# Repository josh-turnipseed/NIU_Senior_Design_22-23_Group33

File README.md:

# NIU Senior Design 2022-2023 Group 33
Analog and Digital Controlled Modular Synthesizer for Audio Synthesis and Signal Processing

The goal of this project was to design and construct a modular Eurorack synthesizer.
The team has designed ten modules that perform the functions of a synthesizer. Those modules are:
- Musical Instrument Digital Interface (MIDI) to Control Voltage (CV)
- Voltage Controlled Oscillator (VCO)
- Voltage Controlled Amplifier (VCA)
- Voltage Controlled Filter (VCF)
- Envelope Generator (EG) ADSR Type
- Low Frequency Oscillator (LFO)
- Mixer
- Multiple
- Attenuverter
- Delay

# Schematics and PCBs
The schematic and board files for all ten modules can be found in the KiCad Schematics folder. In which, are folders for each of the modules. In addition to the KiCad project, schematic, and board files, there is a zip in each module folder which contains all the gerber files required to manufacture the PCBs. This group used JLCPCB, but any manufacture will do.

These files were made using KiCad version 7.0.1, release build

# Front Panels
This group chose to manufacture front panels using FDM 3D printing technologies. Step files can be found in the Steps folder for each of the modules. These files can be loaded into the slicer of your choice. Specifically, this group used Prusaslicer 2.6.0-alpha6 for the embossed text feature. Gcode can be found in the Gcode folder for each of the module front panels with text. The Gcode is for a Prusa i3 MK3S.

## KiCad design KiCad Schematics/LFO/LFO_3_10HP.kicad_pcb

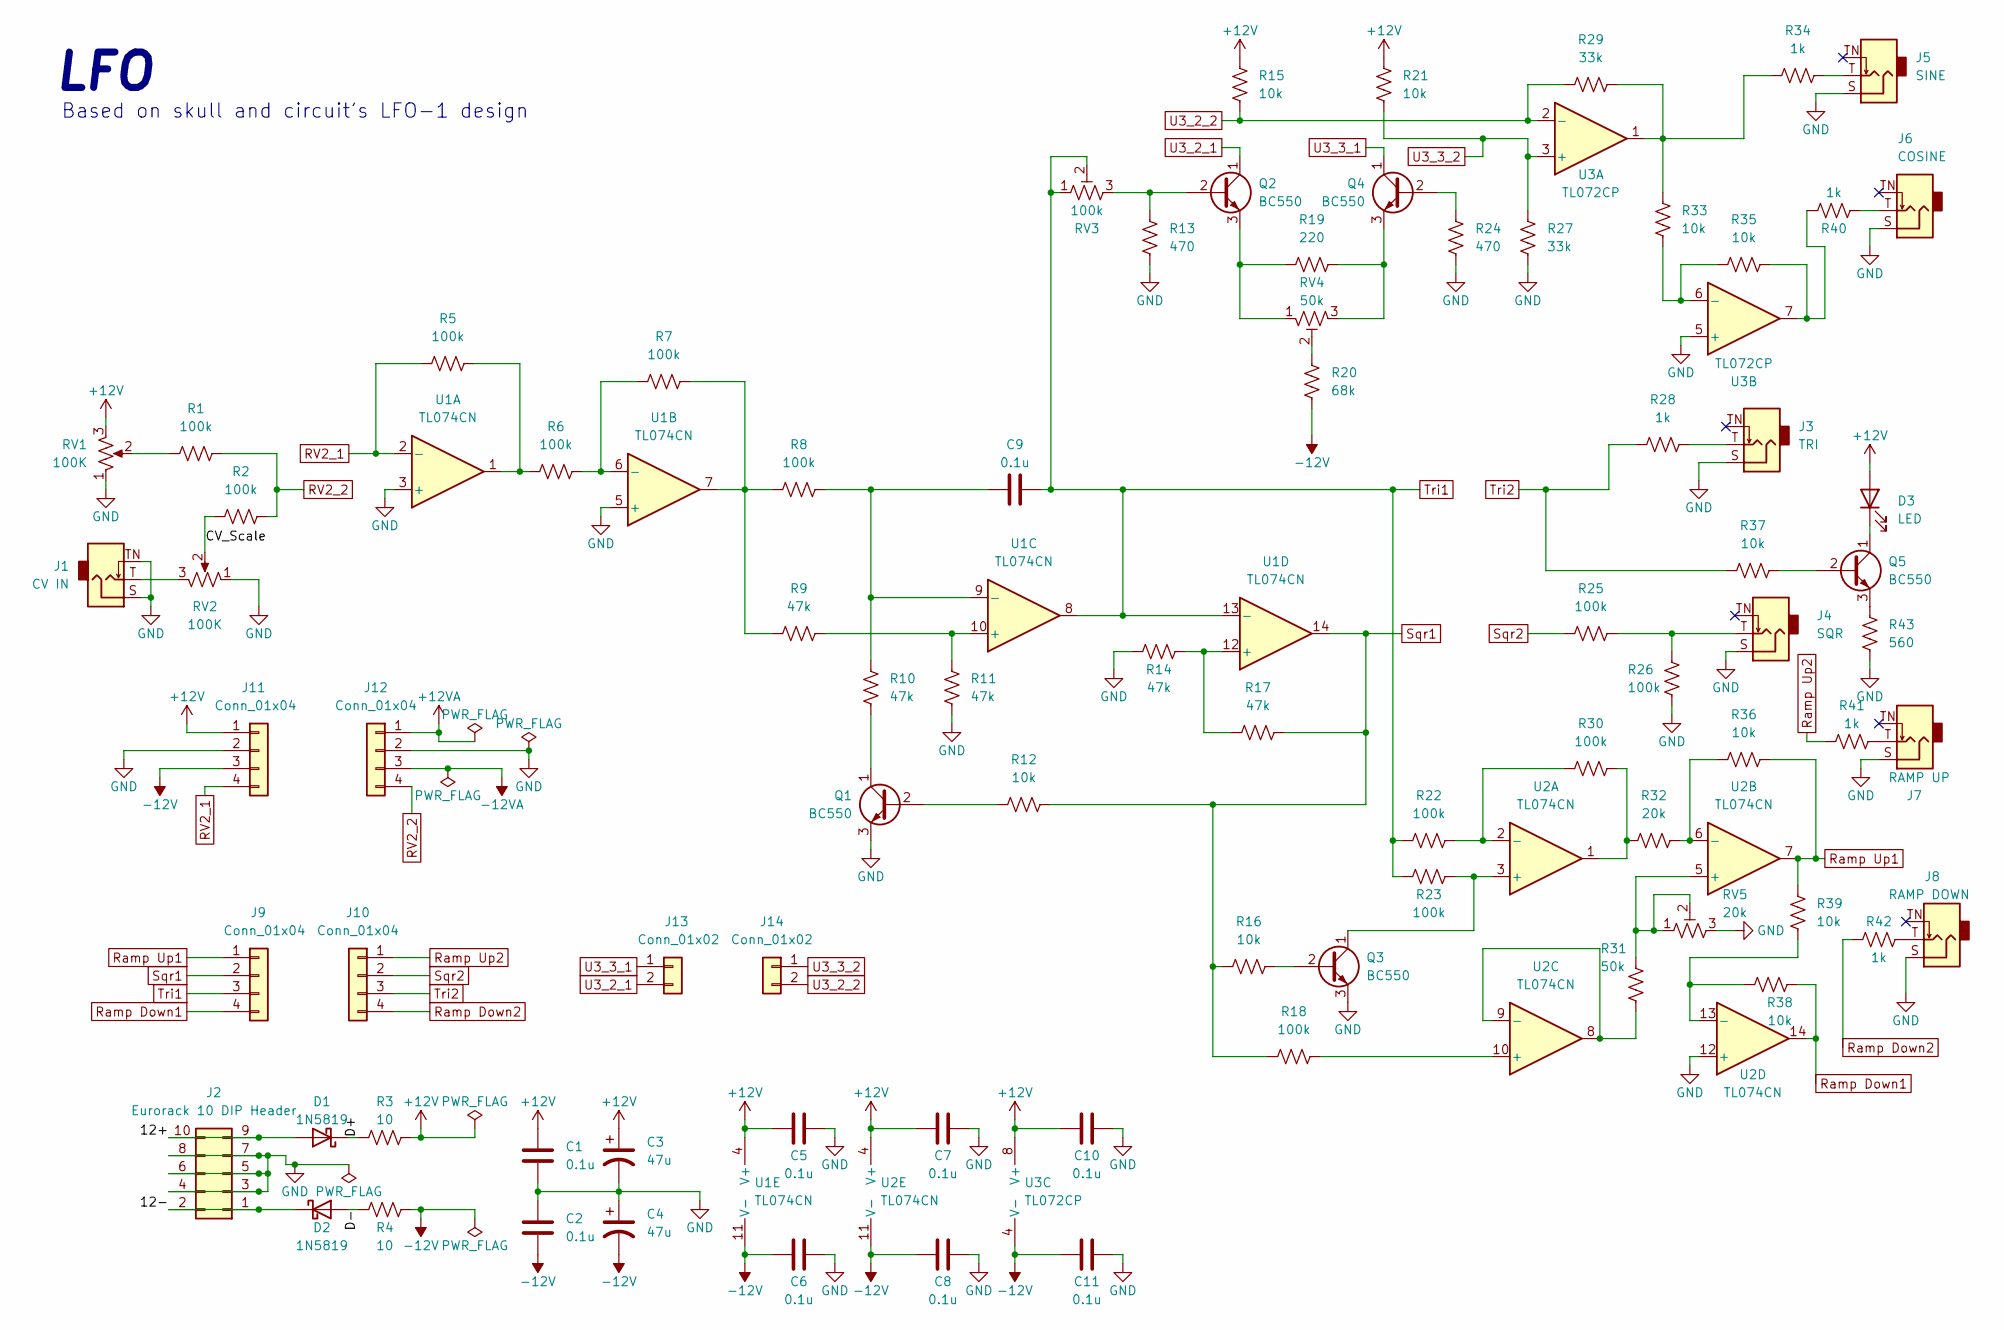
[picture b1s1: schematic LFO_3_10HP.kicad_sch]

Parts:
C1, C2, C5, C6, C7, C8, C9, C10, C11: 0.1u; C_Disc_D4.7mm_W2.5mm_P5.00mm
C3, C4: 47u; CP_Radial_D4.0mm_P2.00mm
D1, D2: 1N5819; D_DO-41_SOD81_P10.16mm_Horizontal
D3: LED; LED_D5.0mm
J1: CV IN; Jack_3.5mm_QingPu_WQP-PJ398SM_Vertical_CircularHoles
J2: Eurorack 10 DIP Header; Eurorack_10_pin_header
J3: TRI; Jack_3.5mm_QingPu_WQP-PJ398SM_Vertical_CircularHoles
J4: SQR; Jack_3.5mm_QingPu_WQP-PJ398SM_Vertical_CircularHoles
J5: SINE; Jack_3.5mm_QingPu_WQP-PJ398SM_Vertical_CircularHoles
J6: COSINE; Jack_3.5mm_QingPu_WQP-PJ398SM_Vertical_CircularHoles
J7: RAMP UP; Jack_3.5mm_QingPu_WQP-PJ398SM_Vertical_CircularHoles
J8: RAMP DOWN; Jack_3.5mm_QingPu_WQP-PJ398SM_Vertical_CircularHoles
J9, J10, J11, J12: Conn_01x04; PinHeader_1x04_P2.54mm_Vertical
J13, J14: Conn_01x02; PinHeader_1x02_P2.54mm_Vertical
Q1, Q2, Q3, Q4, Q5: BC550; TO-92_Inline_Wide
R1, R2, R5, R6, R7, R8, R18, R22, R23, R25, R26, R30: 100k; R_Axial_DIN0207_L6.3mm_D2.5mm_P7.62mm_Horizontal
R3, R4: 10; R_Axial_DIN0207_L6.3mm_D2.5mm_P7.62mm_Horizontal
R9, R10, R11, R14, R17: 47k; R_Axial_DIN0207_L6.3mm_D2.5mm_P7.62mm_Horizontal
R12, R15, R16, R21, R33, R35, R36, R37, R38, R39: 10k; R_Axial_DIN0207_L6.3mm_D2.5mm_P7.62mm_Horizontal
R13, R24: 470; R_Axial_DIN0207_L6.3mm_D2.5mm_P7.62mm_Horizontal
R19: 220; R_Axial_DIN0207_L6.3mm_D2.5mm_P7.62mm_Horizontal
R20: 68k; R_Axial_DIN0207_L6.3mm_D2.5mm_P7.62mm_Horizontal
R27, R29: 33k; R_Axial_DIN0207_L6.3mm_D2.5mm_P7.62mm_Horizontal
R28, R34, R40, R41, R42: 1k; R_Axial_DIN0207_L6.3mm_D2.5mm_P7.62mm_Horizontal
R31: 50k; R_Axial_DIN0207_L6.3mm_D2.5mm_P7.62mm_Horizontal
R32: 20k; R_Axial_DIN0207_L6.3mm_D2.5mm_P7.62mm_Horizontal
R43: 560; R_Axial_DIN0207_L6.3mm_D2.5mm_P7.62mm_Horizontal
RV1, RV2: 100K; Alpha_9mm_Potentiometer_Aligned
RV3: 100k; 3296Y-1-502LF
RV4: 50k; 3296Y-1-502LF
RV5: 20k; 3296Y-1-502LF
U1, U2: TL074CN; DIP794W45P254L1969H508Q14
U3: TL072CP; DIP794W45P254L959H508Q8

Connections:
/12+: D1.2 (A), J2.9, J2.10
/12-: D2.1 (K), J2.1, J2.2
/CV_Scale: R2.1, RV2.2
/D+: D1.1 (K), R3.2
/D-: D2.2 (A), R4.2
GND: C1.1, C2.2, C3.2, C4.1, C5.2, C6.2, C7.2, C8.2, C10.2, C11.2, J1.S, J1.TN, J2.3, J2.4, J2.5, J2.6, J2.7, J2.8, J3.S, J4.S, J5.S, J6.S, J7.S, J8.S, J11.2, J12.2, Q1.3 (E), Q3.3 (E), R11.1, R13.2, R14.1, R24.2, R26.2, R27.2, R43.2, RV1.1, RV2.1, RV5.3, U1.3 (+), U1.5 (+), U2.12 (+), U3.5 (+)
unnamed: C9.1, R8.2, R10.2, U1.9 (-)
unnamed: D3.1 (K), Q5.1 (C)
unnamed: J1.T, RV2.3
unnamed: J3.T, R28.1
unnamed: J4.T, R25.1, R26.1
unnamed: J5.T, R34.1
unnamed: J6.T, R40.1
unnamed: J7.T, R41.1
unnamed: J8.T, R42.1
unnamed: Q1.1 (C), R10.1
unnamed: Q1.2 (B), R12.2
unnamed: Q2.2 (B), R13.1, RV3.3
unnamed: Q2.3 (E), R19.2, RV4.1
unnamed: Q3.1 (C), R23.1, U2.3 (+)
unnamed: Q3.2 (B), R16.1
unnamed: Q4.2 (B), R24.1
unnamed: Q4.3 (E), R19.1, RV4.3
unnamed: Q5.2 (B), R37.1
unnamed: Q5.3 (E), R43.1
unnamed: R1.1, RV1.2
unnamed: R5.2, R6.1, U1.1
unnamed: R6.2, R7.1, U1.6 (-)
unnamed: R7.2, R8.1, R9.1, U1.7
unnamed: R9.2, R11.2, U1.10 (+)
unnamed: R14.2, R17.2, U1.12 (+)
unnamed: R18.1, U2.10 (+)
unnamed: R20.1, RV4.2
unnamed: R22.1, R30.2, U2.2 (-)
unnamed: R29.2, R33.1, R34.2, U3.1
unnamed: R30.1, R32.2, U2.1
unnamed: R31.1, RV5.1, RV5.2, U2.5 (+)
unnamed: R31.2, U2.8, U2.9 (-)
unnamed: R32.1, R36.2, U2.6 (-)
unnamed: R33.2, R35.1, U3.6 (-)
unnamed: R35.2, R40.2, U3.7
unnamed: R38.2, R39.2, U2.13 (-)
RV2_1: J11.4, R5.1, U1.2 (-)
RV2_2: J12.4, R1.2, R2.2
Ramp Down1: J9.4, R38.1, U2.14
Ramp Down2: J10.4, R42.2
Ramp Up1: J9.1, R36.1, R39.1, U2.7
Ramp Up2: J10.1, R41.2
Sqr1: J9.2, R12.1, R16.2, R17.1, R18.2, U1.14
Sqr2: J10.2, R25.2
Tri1: C9.2, J9.3, R22.2, R23.2, RV3.1, RV3.2, U1.8, U1.13 (-)
Tri2: J10.3, R28.2, R37.2
U3_2_1: J13.2, Q2.1 (C)
U3_2_2: J14.2, R15.2, R29.1, U3.2 (-)
U3_3_1: J13.1, Q4.1 (C)
U3_3_2: J14.1, R21.2, R27.1, U3.3 (+)

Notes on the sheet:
LFO
Based on skull and circuit's LFO-1 design

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
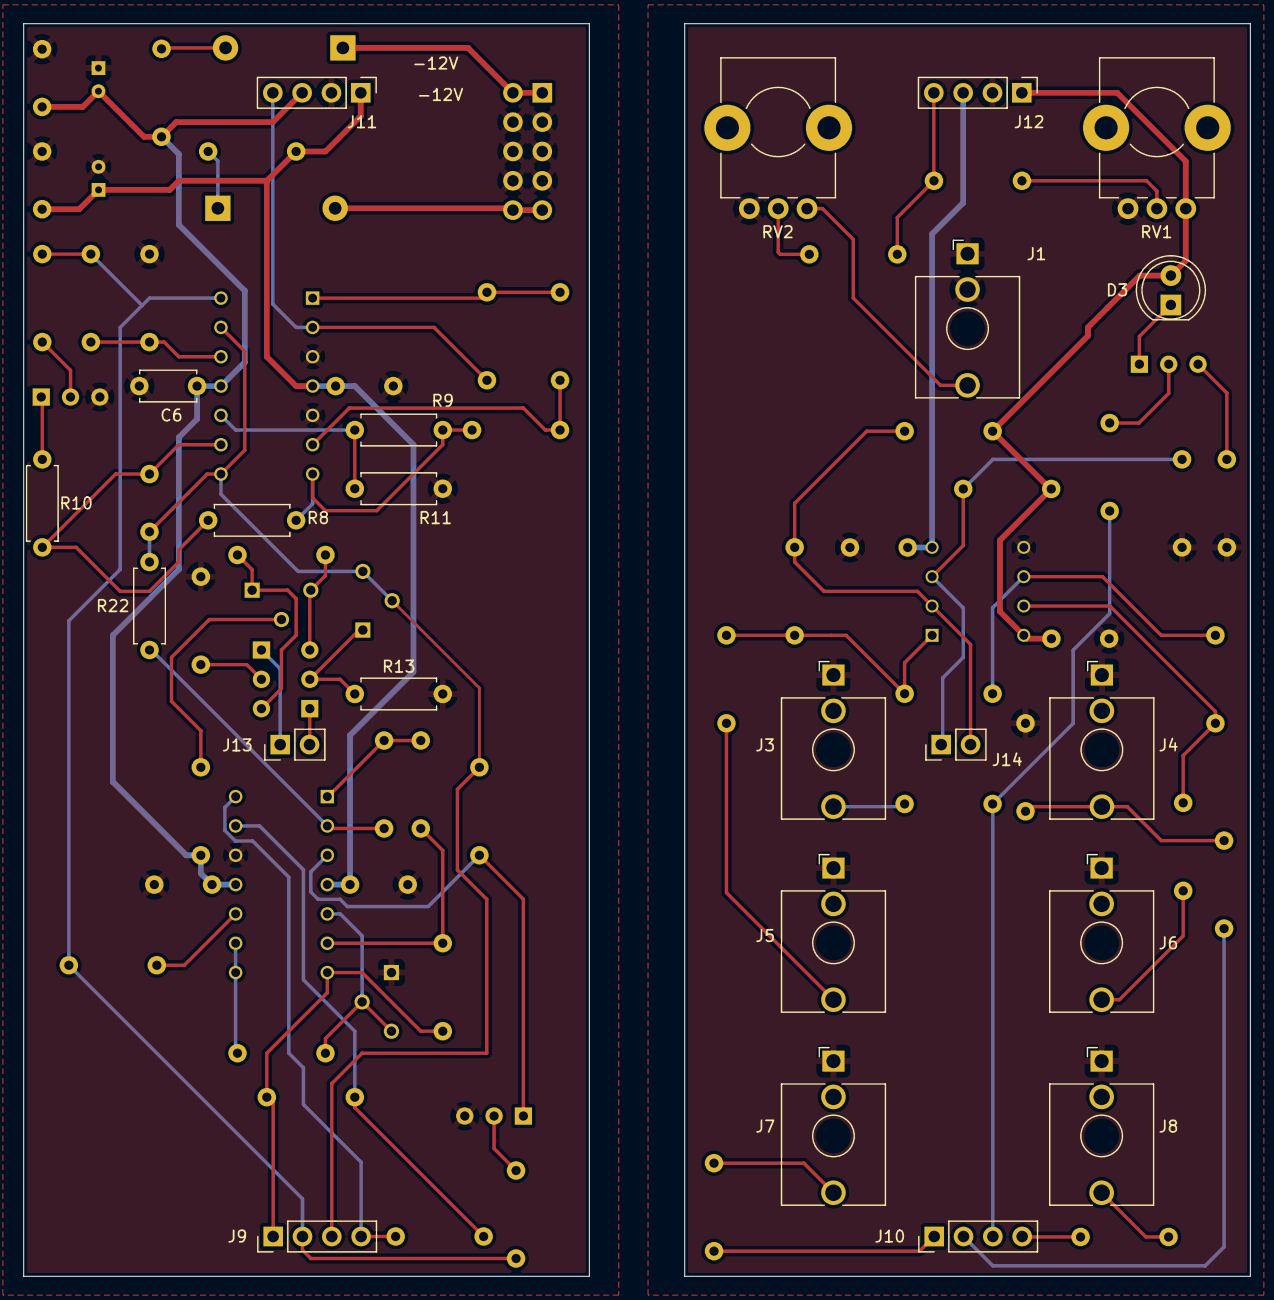
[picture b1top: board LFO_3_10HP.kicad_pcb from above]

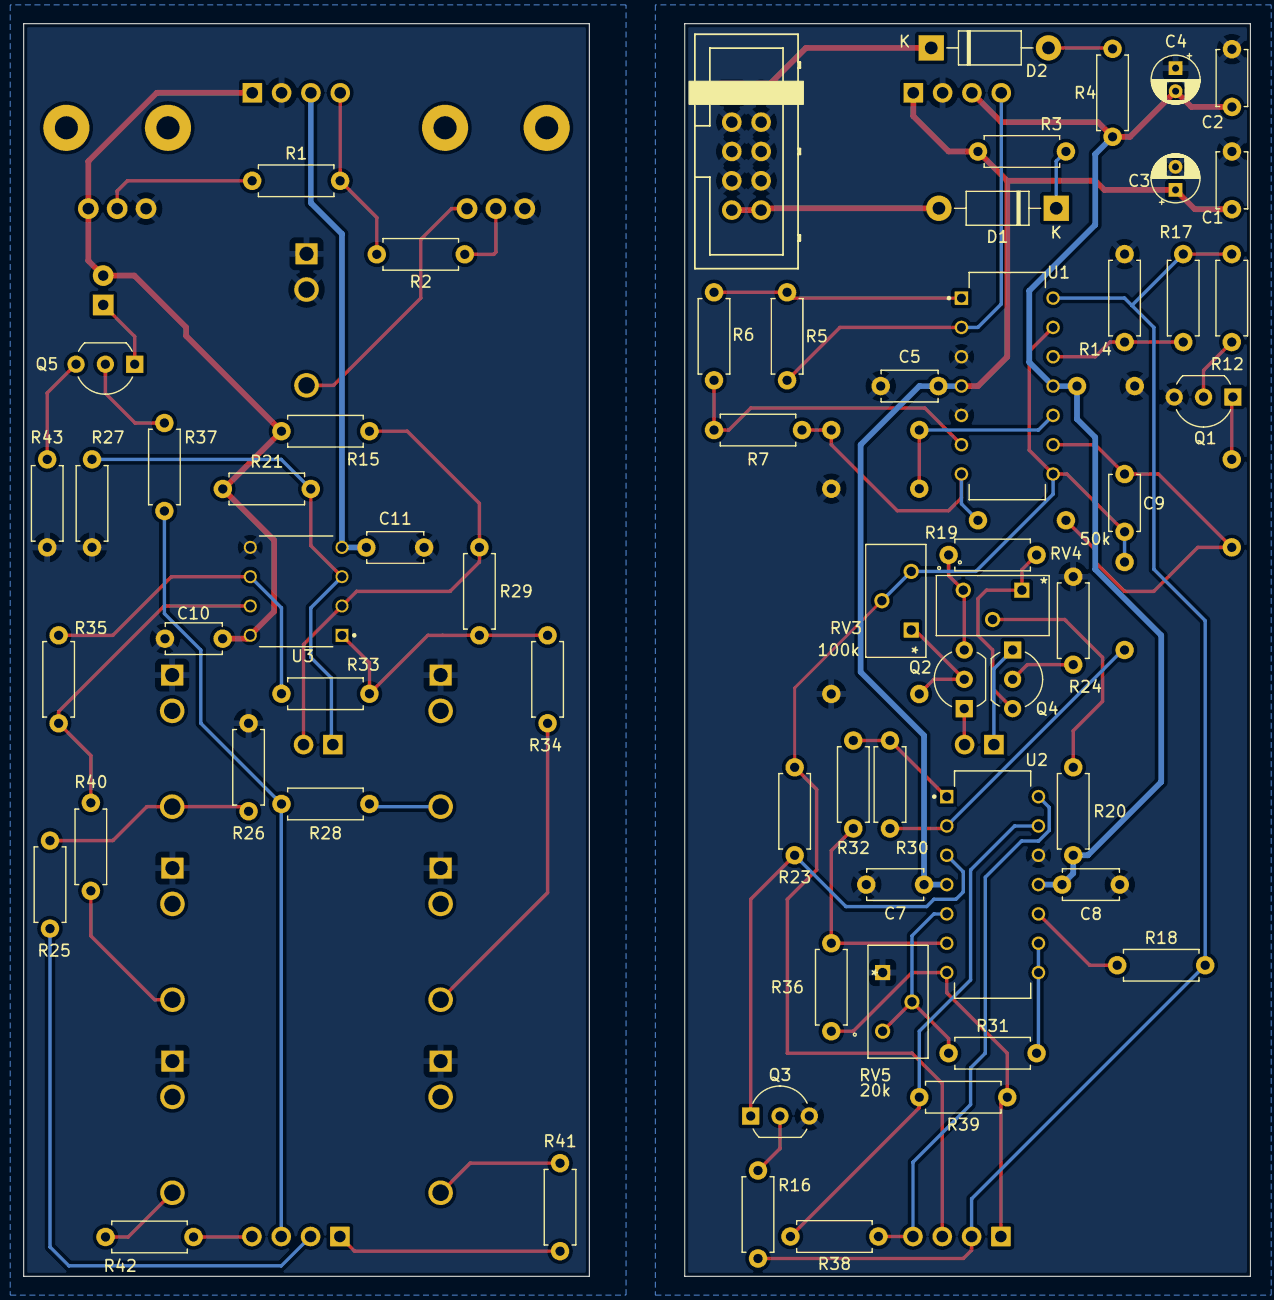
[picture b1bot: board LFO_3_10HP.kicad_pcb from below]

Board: 2 copper layers, 106.3 x 108.5 mm, 84 parts (61 on the bottom side), 60 nets.

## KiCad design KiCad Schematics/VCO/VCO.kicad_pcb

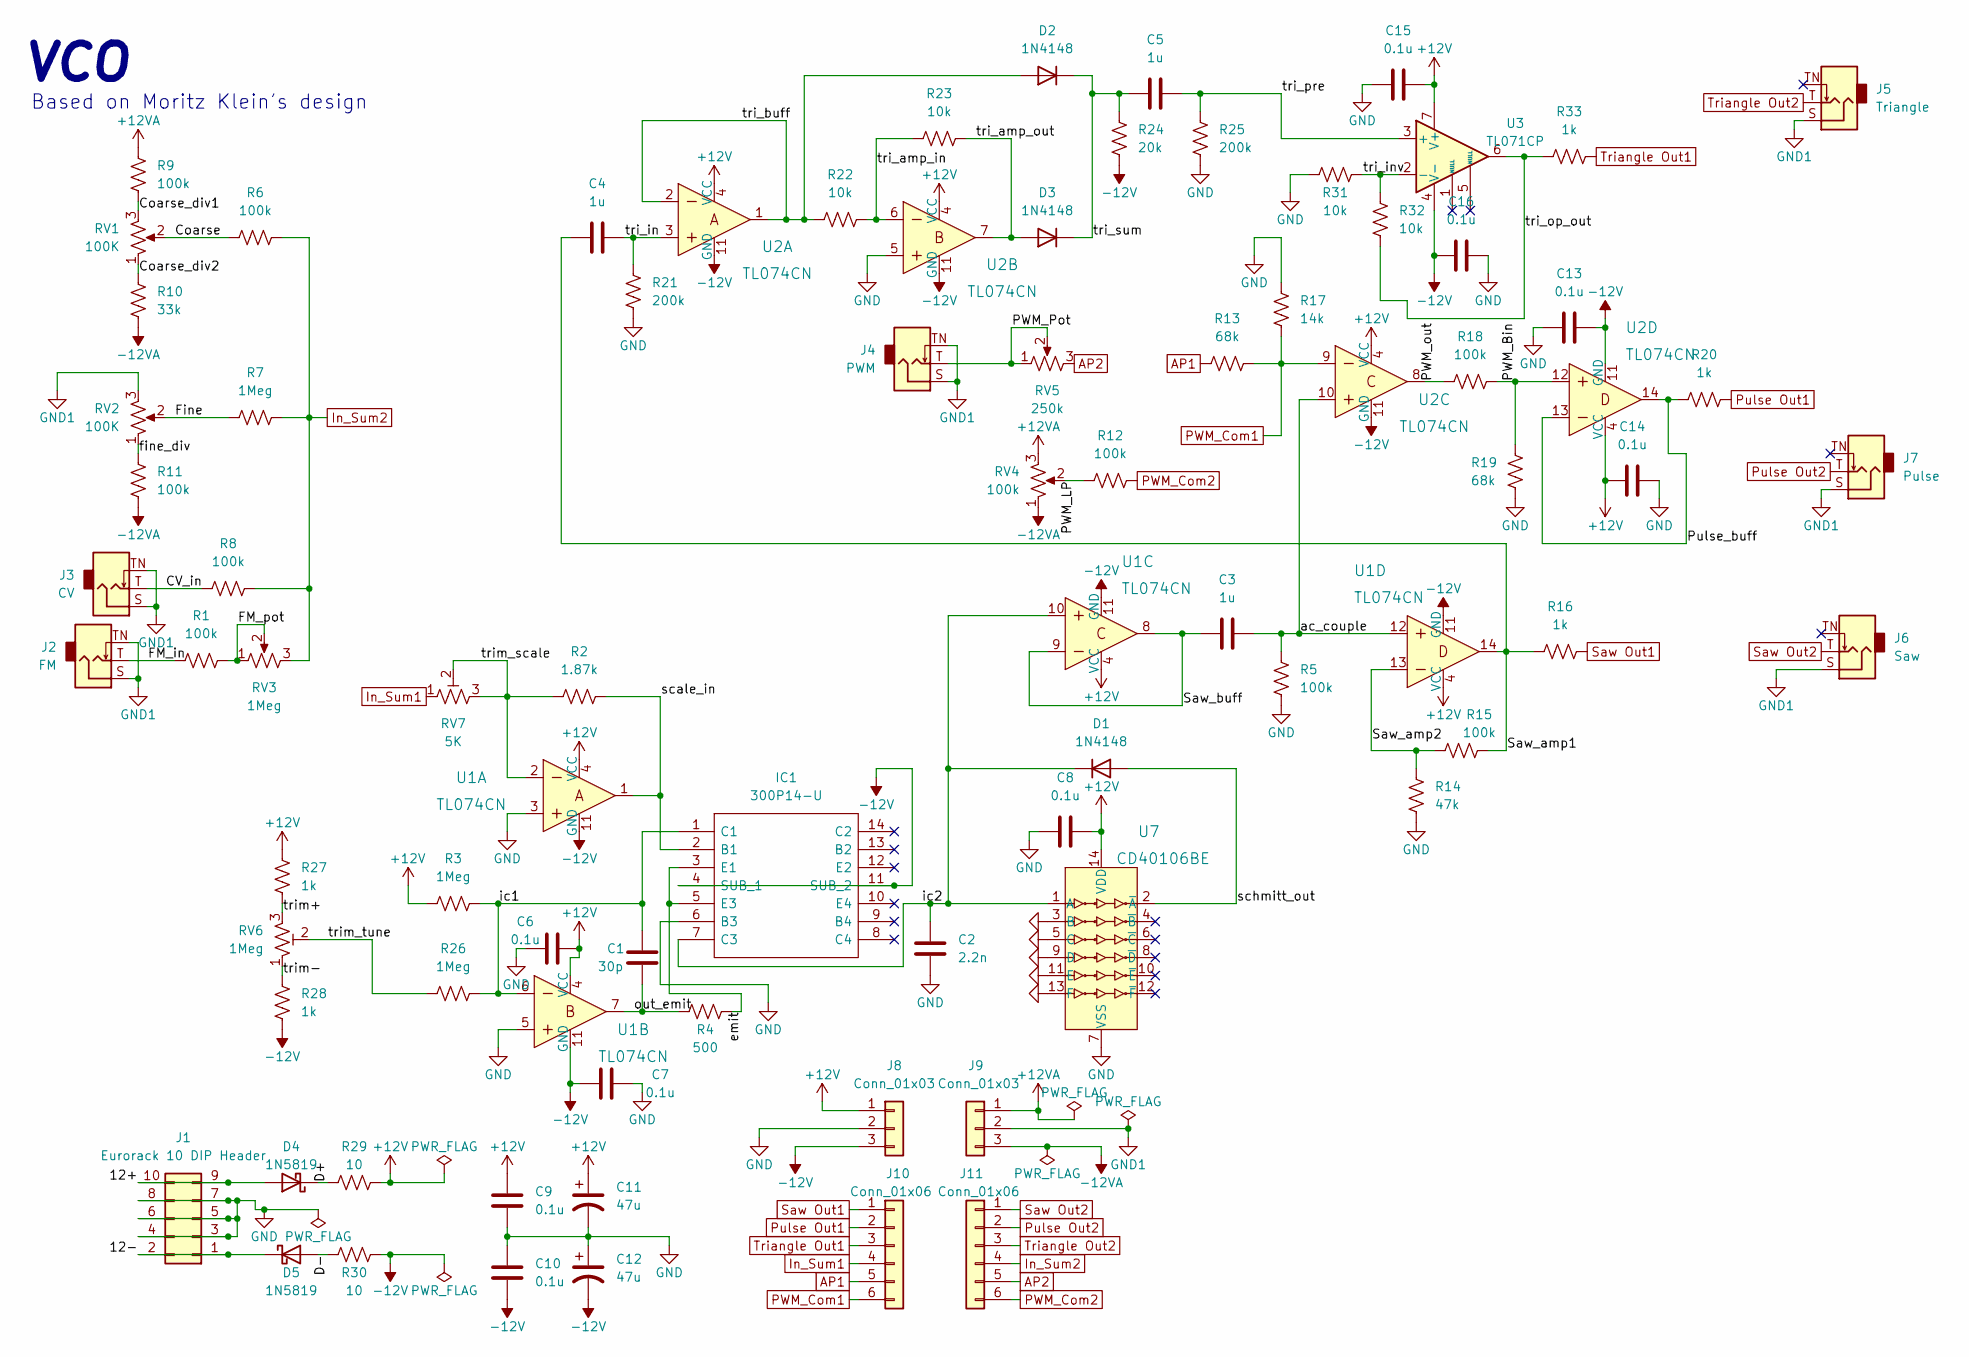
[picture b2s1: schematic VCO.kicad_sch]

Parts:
C1: 30p; C_Disc_D4.7mm_W2.5mm_P5.00mm
C2: 2.2n; C_Disc_D4.7mm_W2.5mm_P5.00mm
C3, C4, C5: 1u; C_Disc_D4.7mm_W2.5mm_P5.00mm
C6, C7, C8, C9, C10, C13, C14, C15, C16: 0.1u; C_Disc_D4.7mm_W2.5mm_P5.00mm
C11, C12: 47u; CP_Radial_D4.0mm_P2.00mm
D1, D2, D3: 1N4148; D_DO-41_SOD81_P10.16mm_Horizontal
D4, D5: 1N5819; D_DO-41_SOD81_P10.16mm_Horizontal
IC1: 300P14-U; DIP-14_W7.62mm
J1: Eurorack 10 DIP Header; Eurorack_10_pin_header
J2: FM; Jack_3.5mm_QingPu_WQP-PJ398SM_Vertical_CircularHoles
J3: CV; Jack_3.5mm_QingPu_WQP-PJ398SM_Vertical_CircularHoles
J4: PWM; Jack_3.5mm_QingPu_WQP-PJ398SM_Vertical_CircularHoles
J5: Triangle; Jack_3.5mm_QingPu_WQP-PJ398SM_Vertical_CircularHoles
J6: Saw; Jack_3.5mm_QingPu_WQP-PJ398SM_Vertical_CircularHoles
J7: Pulse; Jack_3.5mm_QingPu_WQP-PJ398SM_Vertical_CircularHoles
J8: Conn_01x03; PinSocket_1x03_P2.54mm_Vertical
J9: Conn_01x03; PinHeader_1x03_P2.54mm_Vertical
J10: Conn_01x06; PinSocket_1x06_P2.54mm_Vertical
J11: Conn_01x06; PinHeader_1x06_P2.54mm_Vertical
R1, R5, R6, R8, R9, R11, R12, R15, R18: 100k; R_Axial_DIN0207_L6.3mm_D2.5mm_P7.62mm_Horizontal
R2: 1.87k; R_Axial_DIN0207_L6.3mm_D2.5mm_P7.62mm_Horizontal
R3, R7, R26: 1Meg; R_Axial_DIN0207_L6.3mm_D2.5mm_P7.62mm_Horizontal
R4: 500; R_Axial_DIN0207_L6.3mm_D2.5mm_P7.62mm_Horizontal
R10: 33k; R_Axial_DIN0207_L6.3mm_D2.5mm_P7.62mm_Horizontal
R13, R19: 68k; R_Axial_DIN0207_L6.3mm_D2.5mm_P7.62mm_Horizontal
R14: 47k; R_Axial_DIN0207_L6.3mm_D2.5mm_P7.62mm_Horizontal
R16, R20, R27, R28, R33: 1k; R_Axial_DIN0207_L6.3mm_D2.5mm_P7.62mm_Horizontal
R17: 14k; R_Axial_DIN0207_L6.3mm_D2.5mm_P7.62mm_Horizontal
R21, R25: 200k; R_Axial_DIN0207_L6.3mm_D2.5mm_P7.62mm_Horizontal
R22, R23, R31, R32: 10k; R_Axial_DIN0207_L6.3mm_D2.5mm_P7.62mm_Horizontal
R24: 20k; R_Axial_DIN0207_L6.3mm_D2.5mm_P7.62mm_Horizontal
R29, R30: 10; R_Axial_DIN0207_L6.3mm_D2.5mm_P7.62mm_Horizontal
RV1, RV2: 100K; Alpha_9mm_Potentiometer_Aligned
RV3: 1Meg; Alpha_9mm_Potentiometer_Aligned
RV4: 100k; Alpha_9mm_Potentiometer_Aligned
RV5: 250k; Alpha_9mm_Potentiometer_Aligned
RV6: 1Meg; 3296Y1502LF
RV7: 5K; 3296Y1502LF
U1, U2: TL074CN; DIP-14_W3mm
U3: TL071CP; DIP-8_W7.62mm
U7: CD40106BE; DIP-14_W3mm; MPN CD40106BE; Digi-Key_PN 296-3503-5-ND

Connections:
+12V: C6.1, C8.2, C9.2, C11.1, C14.2, C15.1, J8.1, R3.1, R27.2, R29.1, U1.4 (VCC), U2.4 (VCC), U3.7 (V+), U7.14 (VDD)
+12VA: J9.1, R9.2, RV4.3
-12V: C7.2, C10.1, C12.2, C13.1, C16.2, IC1.4 (SUB_1), IC1.11 (SUB_2), J8.3, R24.1, R28.1, R30.1, U1.11 (GND), U2.11 (GND), U3.4 (V-)
-12VA: J9.3, R10.1, R11.1, RV4.1
/12+: D4.2 (A), J1.9, J1.10
/12-: D5.1 (K), J1.1, J1.2
/CV_in: J3.T, R8.1
/Coarse: R6.1, RV1.2
/Coarse_div1: R9.1, RV1.3
/Coarse_div2: R10.2, RV1.1
/D+: D4.1 (K), R29.2
/D-: D5.2 (A), R30.2
/FM_in: J2.T, R1.1
/FM_pot: R1.2, RV3.1, RV3.2
/Fine: R7.1, RV2.2
/PWM_Bin: R18.2, R19.2, U2.12
/PWM_LP: R12.2, RV4.2
/PWM_Pot: J4.T, RV5.1, RV5.2
/PWM_out: R18.1, U2.8
/Pulse_buff: R20.1, U2.13, U2.14
/Saw_amp1: C4.1, R15.2, R16.1, U1.14
/Saw_amp2: R14.1, R15.1, U1.13
/Saw_buff: C3.1, U1.8, U1.9
/ac_couple: C3.2, R5.1, U1.12, U2.10
/emit: IC1.3 (E1), IC1.5 (E3), R4.2
/fine_div: R11.2, RV2.1
/ic1: C1.1, IC1.1 (C1), R3.2, R26.2, U1.6
/ic2: C2.1, D1.1 (K), IC1.7 (C3), U1.10, U7.1 (A)
/out_emit: C1.2, R4.1, U1.7
/scale_in: IC1.2 (B1), R2.2, U1.1
/schmitt_out: D1.2 (A), U7.2 (~A)
/tri_amp_in: R22.1, R23.2, U2.6
/tri_amp_out: D3.2 (A), R23.1, U2.7
/tri_buff: D2.2 (A), R22.2, U2.1, U2.2
/tri_in: C4.2, R21.2, U2.3
/tri_inv: R31.2, R32.2, U3.2 (-)
/tri_op_out: R32.1, R33.1, U3.6
/tri_pre: C5.2, R25.2, U3.3 (+)
/tri_sum: C5.1, D2.1 (K), D3.1 (K), R24.2
/trim+: R27.1, RV6.3
/trim-: R28.2, RV6.1
/trim_scale: R2.1, RV7.2, RV7.3, U1.2
/trim_tune: R26.1, RV6.2
AP1: J10.5, R13.2
AP2: J11.5, RV5.3
GND: C2.2, C6.2, C7.1, C8.1, C9.1, C10.2, C11.2, C12.1, C13.2, C14.1, C15.2, C16.1, IC1.6 (B3), J1.3, J1.4, J1.5, J1.6, J1.7, J1.8, J8.2, R5.2, R14.2, R17.2, R19.1, R21.1, R25.1, R31.1, U1.3, U1.5, U2.5, U7.3 (B), U7.5 (C), U7.7 (VSS), U7.9 (D), U7.11 (E), U7.13 (F)
GND1: J2.S, J2.TN, J3.S, J3.TN, J4.S, J4.TN, J5.S, J6.S, J7.S, J9.2, RV2.3
In_Sum1: J10.4, RV7.1
In_Sum2: J11.4, R6.2, R7.2, R8.2, RV3.3
PWM_Com1: J10.6, R13.1, R17.1, U2.9
PWM_Com2: J11.6, R12.1
Pulse Out1: J10.2, R20.2
Pulse Out2: J7.T, J11.2
Saw Out1: J10.1, R16.2
Saw Out2: J6.T, J11.1
Triangle Out1: J10.3, R33.2
Triangle Out2: J5.T, J11.3

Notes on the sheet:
VCO
Based on Moritz Klein's design

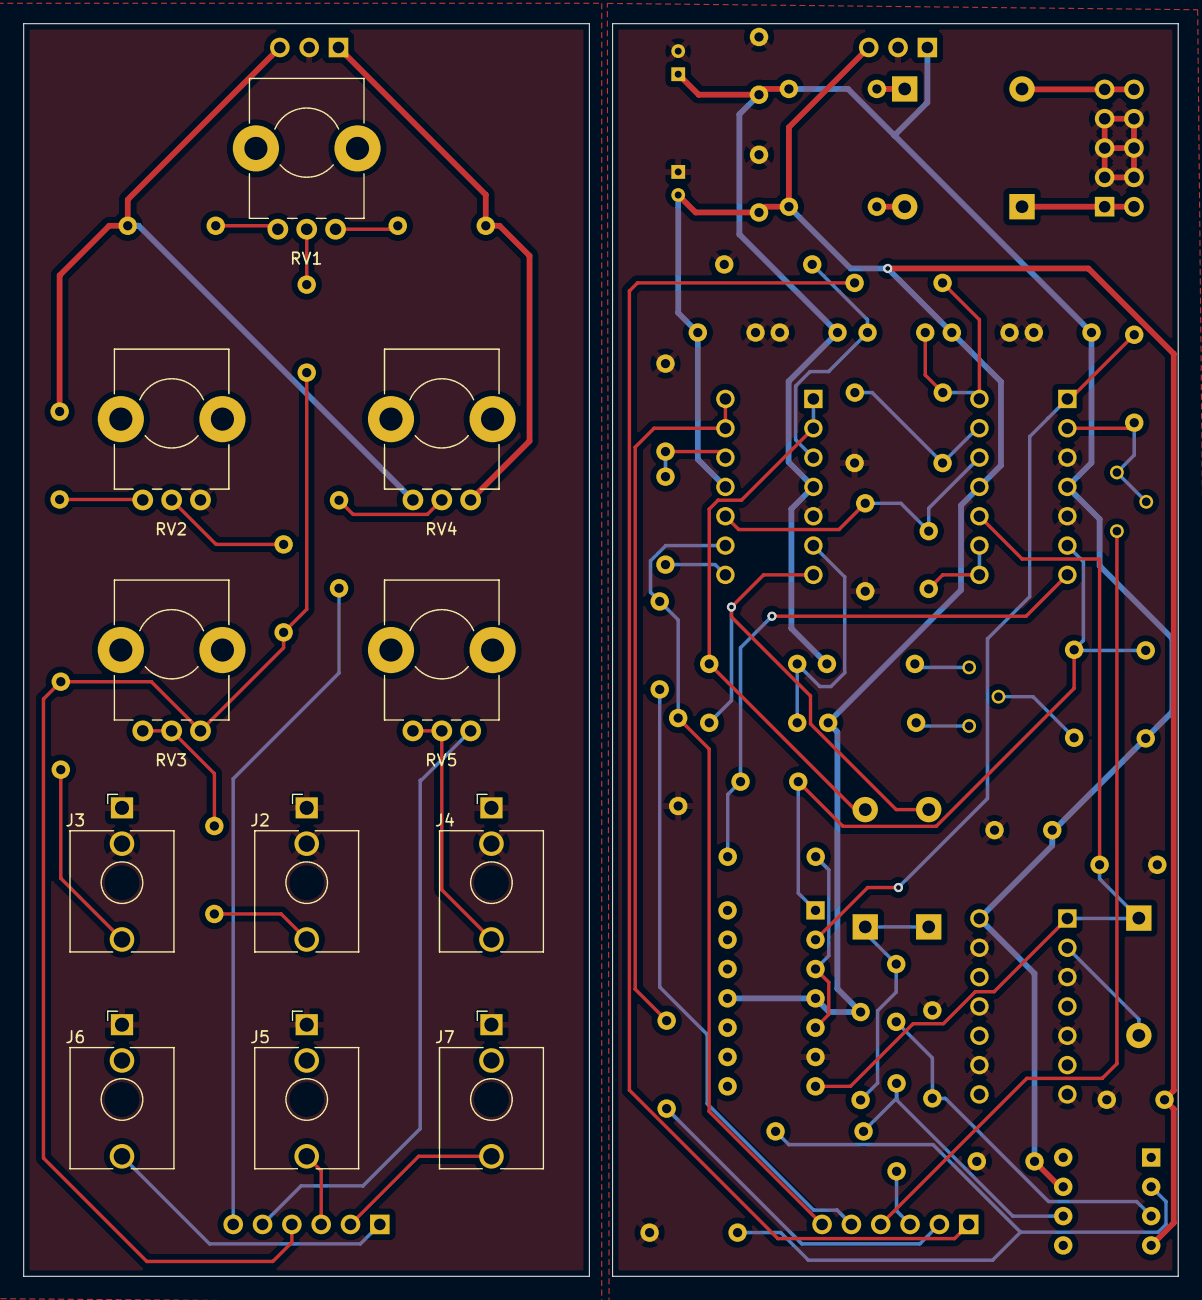
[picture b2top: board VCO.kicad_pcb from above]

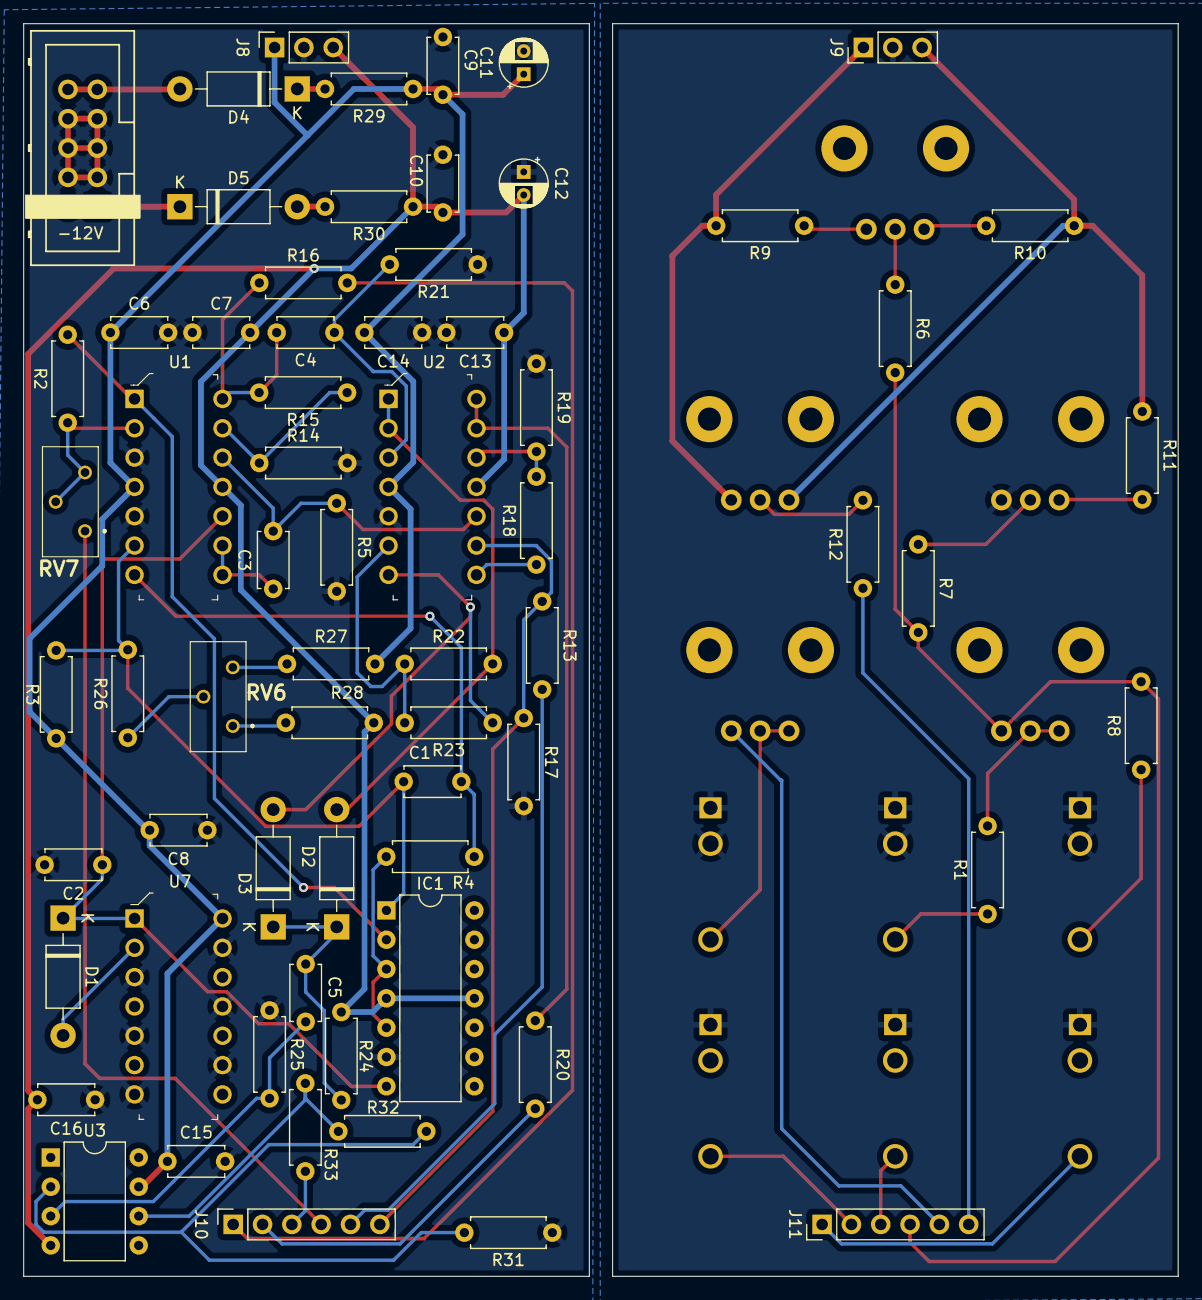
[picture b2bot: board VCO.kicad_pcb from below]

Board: 2 copper layers, 100.0 x 108.5 mm, 77 parts (66 on the bottom side), 57 nets.

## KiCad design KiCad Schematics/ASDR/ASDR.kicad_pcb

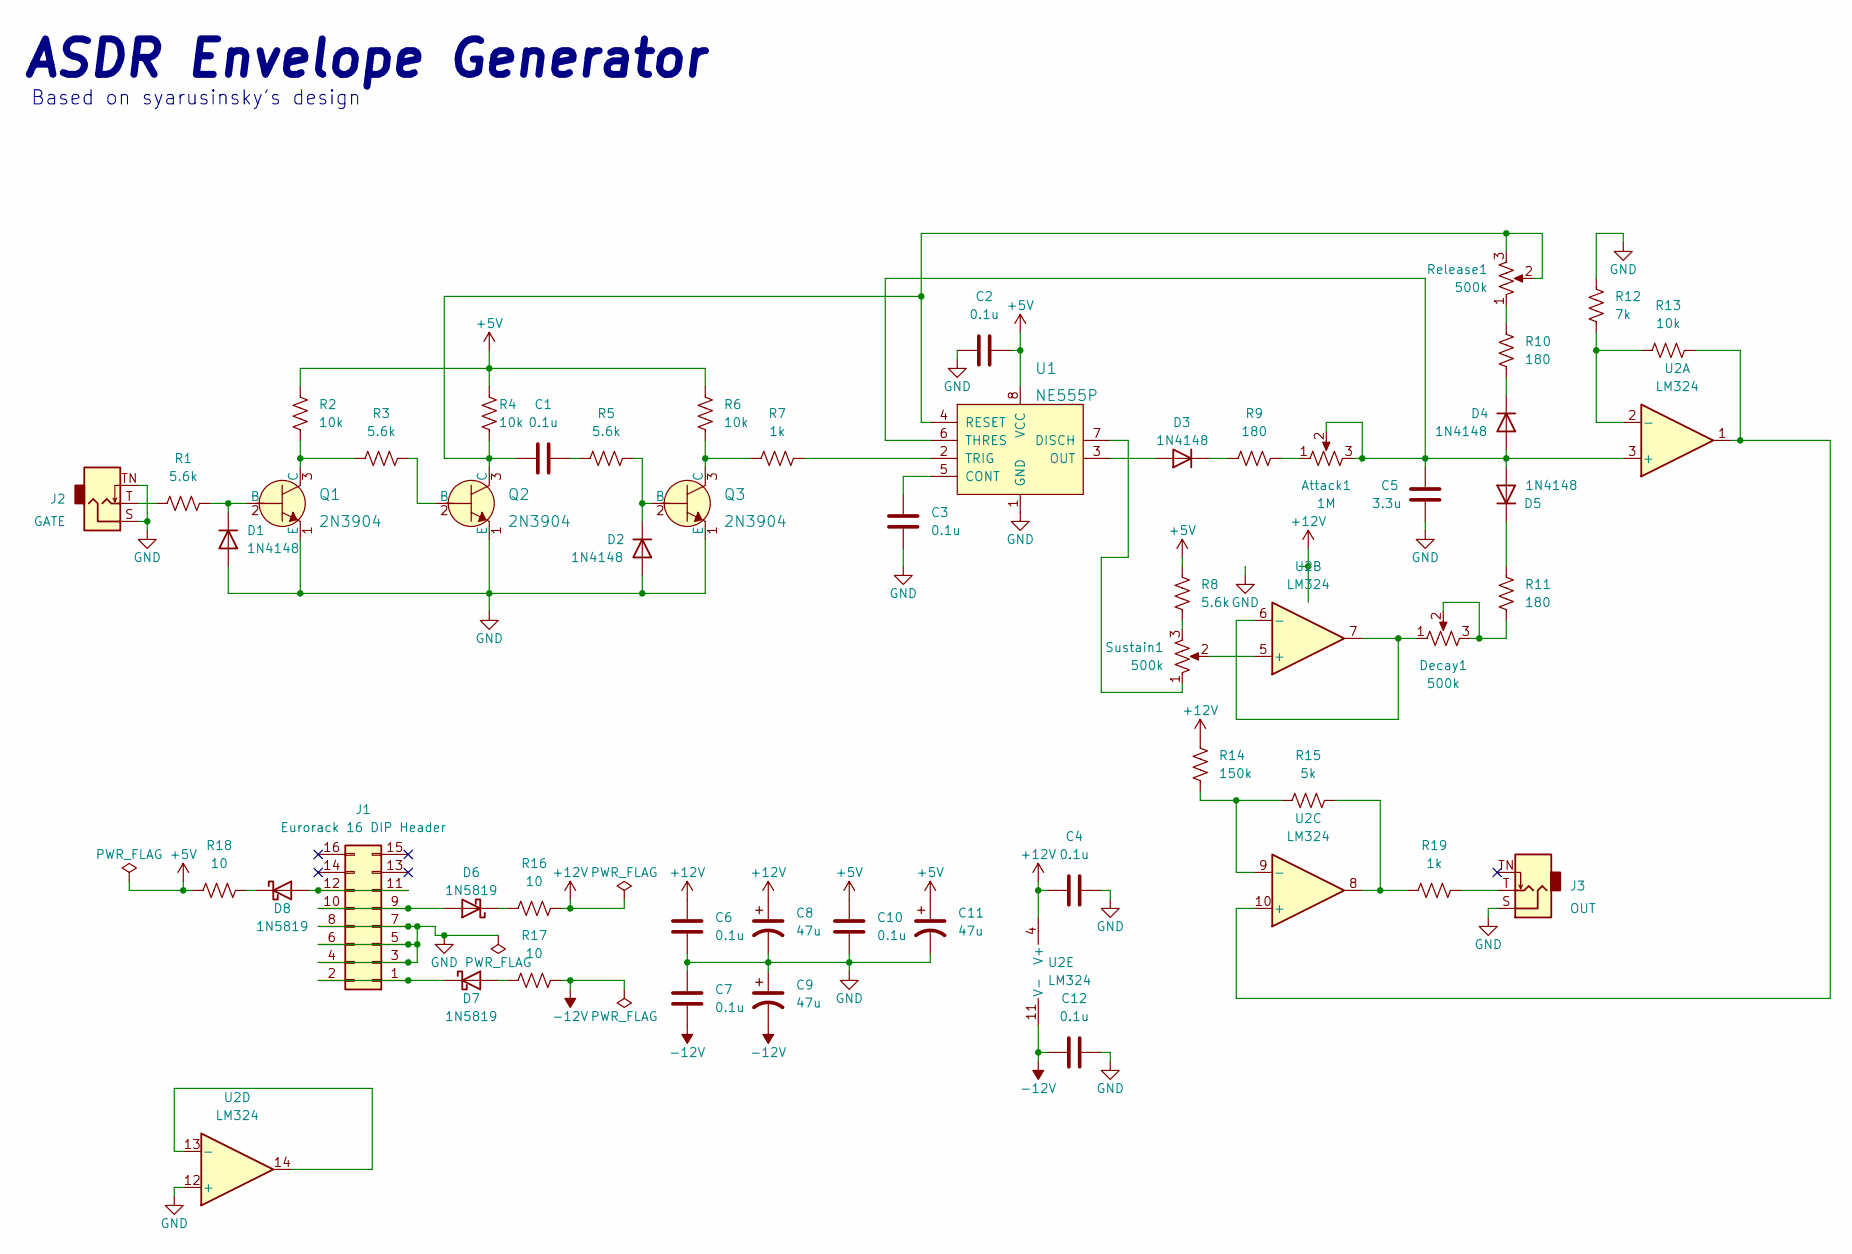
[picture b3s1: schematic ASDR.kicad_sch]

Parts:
Attack1: 1M; Alpha_9mm_Potentiometer
C1, C2, C3, C4, C6, C7, C10, C12: 0.1u; C_Disc_D4.7mm_W2.5mm_P5.00mm
C5: 3.3u; C_Disc_D4.7mm_W2.5mm_P5.00mm
C8, C9, C11: 47u; CP_Radial_D4.0mm_P2.00mm
D1, D2, D3, D4, D5: 1N4148; D_DO-41_SOD81_P3.81mm_Vertical_KathodeUp
D6, D7, D8: 1N5819; D_DO-41_SOD81_P3.81mm_Vertical_KathodeUp
Decay1: 500k; Alpha_9mm_Potentiometer
J1: Eurorack 16 DIP Header; Eurorack_16_pin_header
J2: GATE; Jack_3.5mm_QingPu_WQP-PJ398SM_Vertical_CircularHoles
J3: OUT; Jack_3.5mm_QingPu_WQP-PJ398SM_Vertical_CircularHoles
Q1, Q2, Q3: 2N3904; TO-92L_Inline_Wide; MPN 2N3904; Digi-Key_PN 2N3904CS-ND
R1, R3, R5, R8: 5.6k; R_Axial_DIN0207_L6.3mm_D2.5mm_P2.54mm_Vertical
R2, R4, R6, R13: 10k; R_Axial_DIN0207_L6.3mm_D2.5mm_P2.54mm_Vertical
R7, R19: 1k; R_Axial_DIN0207_L6.3mm_D2.5mm_P2.54mm_Vertical
R9, R10, R11: 180; R_Axial_DIN0207_L6.3mm_D2.5mm_P2.54mm_Vertical
R12: 7k; R_Axial_DIN0207_L6.3mm_D2.5mm_P2.54mm_Vertical
R14: 150k; R_Axial_DIN0207_L6.3mm_D2.5mm_P2.54mm_Vertical
R15: 5k; R_Axial_DIN0207_L6.3mm_D2.5mm_P2.54mm_Vertical
R16, R17, R18: 10; R_Axial_DIN0207_L6.3mm_D2.5mm_P2.54mm_Vertical
Release1: 500k; Alpha_9mm_Potentiometer
Sustain1: 500k; Alpha_9mm_Potentiometer
U1: NE555P; DIP-8_W7.62mm; MPN NE555P; Digi-Key_PN 296-1411-5-ND
U2: LM324; DIP-14_W7.62mm

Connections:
+5V: C2.2, C10.2, C11.1, R2.2, R4.2, R6.2, R8.2, R18.2, U1.8 (VCC)
+12V: C4.1, C6.2, C8.1, R14.1, R16.1, U2.4 (V+)
-12V: C7.1, C9.2, C12.1, R17.1, U2.11 (V-)
GND: C2.1, C3.1, C4.2, C5.1, C6.1, C7.2, C8.2, C9.1, C10.1, C11.2, C12.2, D1.2 (A), D2.2 (A), J1.3, J1.4, J1.5, J1.6, J1.7, J1.8, J2.S, J2.TN, J3.S, Q1.1 (E), Q2.1 (E), Q3.1 (E), R12.1, U1.1 (GND), U2.12 (+); also elsewhere on the board
unnamed: Attack1.1, R9.1
unnamed: Attack1.2, Attack1.3, C5.2, D4.2 (A), D5.2 (A), U1.6 (THRES), U2.3 (+)
unnamed 6: C1.1, Q2.3 (C), R4.1, Release1.2, Release1.3, U1.4 (RESET); also elsewhere on the board
unnamed: C1.2, R5.1
unnamed: C3.2, U1.5 (CONT)
unnamed: D1.1 (K), Q1.2 (B), R1.2
unnamed: D2.1 (K), Q3.2 (B), R5.2
unnamed: D3.1 (K), R9.2
unnamed: D3.2 (A), U1.3 (OUT)
unnamed: D4.1 (K), R10.2
unnamed: D5.1 (K), R11.1
unnamed: D6.1 (K), R16.2
unnamed: D6.2 (A), J1.9, J1.10
unnamed: D7.1 (K), J1.1, J1.2
unnamed: D7.2 (A), R17.2
unnamed: D8.1 (K), R18.1
unnamed: D8.2 (A), J1.11, J1.12
unnamed: Decay1.1, U2.6 (-), U2.7
unnamed: Decay1.2, Decay1.3, R11.2
unnamed: J2.T, R1.1
unnamed: J3.T, R19.2
unnamed: Q1.3 (C), R2.1, R3.1
unnamed 26: Q2.2 (B), R3.2; also elsewhere on the board
unnamed: Q3.3 (C), R6.1, R7.2
unnamed: R7.1, U1.2 (TRIG)
unnamed: R8.1, Sustain1.3
unnamed: R10.1, Release1.1
unnamed: R12.2, R13.1, U2.2 (-)
unnamed: R13.2, U2.1, U2.10 (+)
unnamed: R14.2, R15.1, U2.9 (-)
unnamed: R15.2, R19.1, U2.8
unnamed: Sustain1.1, U1.7 (DISCH)
unnamed: Sustain1.2, U2.5 (+)
unnamed: U2.13 (-), U2.14

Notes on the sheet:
Based on syarusinsky's design
ASDR Envelope Generator

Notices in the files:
parts and their libraries:
Copyright 2021 Accelerated Designs. All rights reserved.
